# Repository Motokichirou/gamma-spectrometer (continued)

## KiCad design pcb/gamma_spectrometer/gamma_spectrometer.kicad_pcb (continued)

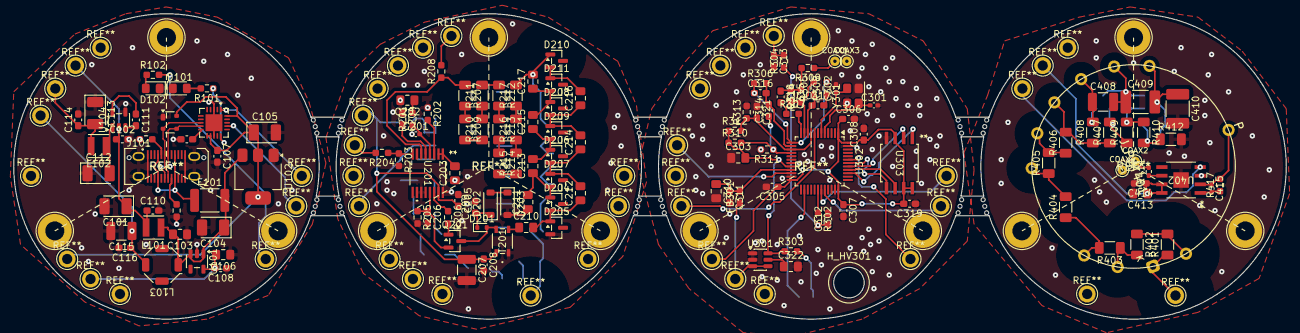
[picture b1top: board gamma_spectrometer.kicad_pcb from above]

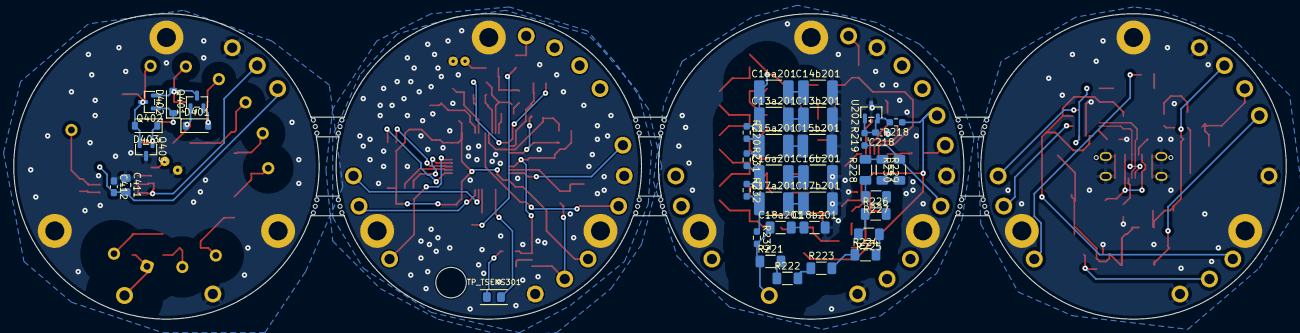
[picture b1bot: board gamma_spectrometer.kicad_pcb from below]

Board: 2 copper layers, 187.5 x 45.0 mm, 183 parts (39 on the bottom side), 115 nets.

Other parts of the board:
COAX1, COAX2, COAX3, COAX4: COAX_PIN_D0.5
H_HV301: HOLE_HV_WIRE_D5.0
PANEL1: PANEL_MOUSEBITES
TP_TSENS301: TP_TSENS_2x0805

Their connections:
AMP_OUT: COAX1.1, COAX2.1; also elsewhere on the board
GND: COAX3.1, COAX4.1; also elsewhere on the board
TSENS_IN: TP_TSENS301.2; also elsewhere on the board
TSENS_PWR: TP_TSENS301.1; also elsewhere on the board

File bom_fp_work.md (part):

# BOM — финальное состояние

> **Статус:** ВСЕ КОМПОНЕНТЫ НАЗНАЧЕНЫ ✅ (включая J_PMT401 — футпринт `J_PMT401_R1307-01` сделан, Ø30)
> Свежий нетлист: `pcb/gamma_spectrometer.net` (2026-06-24, 177 компонентов: 74 конд. + 63 рез. + активные/прочие)
> ⚠ **Правки 2026-08-07 ещё НЕ в нетлисте** (схему правит пользователь): R313 2к→14.7к, R311 5.9к→909,
> U301 TL431→REF35250 (SOT-23-6), R301 удалён, C303 100нФ→1мкФ, добавлен C322 1мкФ.
> После правки схемы: 75 конденсаторов, 62 резистора, всего 177.
> Свежий BOM: см. ниже / экспорт из KiCad

---

## Сводный BOM (финальный)

### Конденсаторы — 17 уникальных MPN, 74 шт

| Refs | Qty | Value | MPN | Footprint |
|---|---|---|---|---|
| C13a201, C13b201, C14a201, C14b201, C15a201, C15b201, C16a201, C16b201, C17a201, C17b201, C410 | 11 | 0.1uF / 1кВ | C1812X104K102T (Holy Stone) | C_1812_HandSolder |
| C18a201, C18b201 | 2 | 220pF / 1кВ C0G | CC1206JKNPOCBN221 (Yageo) | C_1206_HandSolder |
| C101, C104, C105, C112, C113 | 5 | 10uF тант. | TR3B106K010C0750 (Vishay) | CP_EIA-3528-21_Kemet-B_HandSolder |
| C102, C107-C111, C114, C116, C204, C205, C208, C218, C304-C309, C311-C314, C317, C319-C321, C412, C414 | 28 | 0.1uF X7R | CC0603JRX7R9BB104 (Yageo) | C_0603_HandSolder |
| C103, **C303**, **C322** | 3 | 1uF X7R | CC0805JKX7R9BB105 (Yageo) | C_0805_HandSolder — C303 выход REF35250 (обязателен 0.1…10 мкФ), C322 на вывод NR |
| C106, C310, C411, C413 | 4 | 4.7uF X5R | GRM21BR61C475KA88L (Murata) | C_0805_HandSolder |
| C115, C207 | 2 | 47uF X7R | GRM32ER71A476KE15L (Murata) | C_1210_HandSolder |
| C202 | 1 | 33nF X7R | CC0805JRX7R9BB333 (Yageo) | C_0805_HandSolder |
| C203 | 1 | 0.47uF X7R | CC0805JKX7R9BB474 (Yageo) | C_0805_HandSolder |
| C206, C315, C318 | 3 | 100pF C0G | CC0603JRNPO9BN101 (Yageo) | C_0603_HandSolder |
| C201 | 1 | 22pF C0G 50В | GRM1555C1H220JA01D (Murata) | C_0402_HandSolder — C_COMP2, добавлен 2026-09-20 |
| C209 | 1 | 10nF X7R — **заменить на 100 В** | CC0603KRX7R9BB103 (Yageo, 50 В) ⚠ | C_0603_HandSolder → 0805/100В |
| C210-C217 | 8 | 1nF / 500В C0G | CC0805JKNPOBBN102 (Yageo) | C_0805_HandSolder — ⚠ размах на ступень 310…385 В (4 ступени!), запас 1.3× при 1500 В |
| C301, C302 | 2 | 18pF C0G | CC0402FRNPO9BN180 (Yageo) | C_0402_HandSolder |
| C316 | 1 | 510pF C0G | CC0603FRNPO9BN511 (Yageo) | C_0603_HandSolder |
| C408 | 1 | 22nF / 1кВ | CC1210KKX7RCBB223 (Yageo) | C_1210_HandSolder |
| C409 | 1 | 47nF / 1кВ | GRM43DR73A473KW01L (Murata) | C_1812_HandSolder |
| C415 (Cf, TIA) | 1 | 4.7pF C0G NP0 | GRM1555C1H4R7CA01D (Murata) | C_0402_HandSolder |

### Резисторы — стандартные 0603 (1%, низковольтные)

| Refs | Qty | Value | MPN | Серия |
|---|---|---|---|---|
| R101, R102 | 2 | 330R | RT0603BRD07330RL | Yageo RT (thin film) |
| R201 | 1 | 1M | RT0603BRD071ML | Yageo RT (thin film) |
| R202 | 1 | 180k | RC0603FR-07180KL | Yageo RC |
| R203, R220, R231, R232 | 4 | 100k | RC0603FR-07100KL | Yageo RC |
| R204, R302-R305, R307, R309, R408, R411, R413 | 10 | 10k | RC0603FR-0710KL | Yageo RC (R303 = Pt1000 pull-up) |
| R205 | 1 | 0.1R | RL0603FR-070R1L | Yageo RL (current sense) |
| R206, R233 | 2 | 10R | AC0603FR-0710RL | Yageo AC (anti-surge) |
| R208 | 1 | 2.2M | RC0603FR-072M2L | Yageo RC |
| R218 | 1 | 1.2k | RC0603FR-071K2L | Yageo RC |
| R219 | 1 | 110k | RC0603FR-07110KL | Yageo RC |
| ~~R301~~ | — | ~~330R~~ | — | **УДАЛЁН 2026-08-07**: балласт шунта TL431 не нужен последовательной опоре REF35250 |
| R306, R308 | 2 | 1k | RC0603FR-071KL | Yageo RC |
| R310 | 1 | 22k | RC0603FR-0722KL | Yageo RC |
| R311 | 1 | **909R** | RC0603FR-07909RL | Yageo RC (было 5.9k; смена полярности 2026-08-07) |
| R312 | 1 | 8.2k | RC0603FR-078K2L | Yageo RC |
| R313 | 1 | **14.7k** | RC0603FR-0714K7L | Yageo RC (было 2k; смена полярности 2026-08-07) |
| R417 (Rf, TIA) | 1 | 499R | RC0603FR-07499RL | Yageo RC (вход TIA; Rin/Rg R415/R416 убраны) |
| R_CC101, R_CC102 | 2 | 5.1k | RC0603FR-075K1L | Yageo RC |

**Все 0603 footprint:** Resistor_SMD:R_0603_1608Metric_Pad0.98x0.95mm_HandSolder

### Резисторы — высоковольтные 1206

| Refs | Qty | Value | MPN | Серия |
|---|---|---|---|---|
| R207, R209-R217 | 10 | 100M | RC1206JR-07100ML (5%) | Yageo RC |
| R221-R230 | 10 | 6.8M | RC1206FR-076M8L (1%) | Yageo RC |
| R401, R402 | 2 | 750k | RC1206FR-07750KL | Yageo RC |
| R403-R406 | 4 | 680k | RC1206FR-07680KL | Yageo RC |
| R407, R408 | 2 | 1.3M | RC1206FR-071M3L | Yageo RC (база+эмиттер буфера Q401, пересборка по Fig 5-15) |
| R409 | 1 | 1.6M | RC1206FR-071M6L | Yageo RC |
| R410 | 1 | 2M | RC1206FR-072ML | Yageo RC |
| R412 | 1 | 2M | RC1206FR-072ML | Yageo RC (фикс C1: R414/mid_P убраны) |

**Все 1206 footprint:** Resistor_SMD:R_1206_3216Metric_Pad1.30x1.75mm_HandSolder

### Активные / разное

| Refs | Qty | Value | MPN | Footprint |
|---|---|---|---|---|
| D101 | 1 | LED синий | FYLS-0805UBC (Foryard) | LED_0805_HandSolder |
| D102 | 1 | LED зелёный | 150080GS75000 (Würth) | LED_0805_HandSolder |
| D201 | 1 | BAS516 | BAS516 (YJ) | D_SOD-523 |
| D202, D203 | 2 | BZT52C18 | BZT52C18 (Diotec) | Nexperia_CFP3_SOD-123W ⚠ проверить |
| D204-D211 | 8 | BAV23S | BAV23S (Nexperia) | SOT-23 |
| D401-D403 | 3 | 1N4148W | 1N4148W (onsemi/Diotec) | Diode_SMD:D_SOD-123 (защита B-E буферов Q401-403) |
| F101 | 1 | PTC 500мА | MF-MSMF050-2 (JEMETE) | Fuse_1812_HandSolder |
| FB301 | 1 | 120Ω@100МГц | BLM18EG121SN1D (Murata) | L_0603_HandSolder |
| J101 | 1 | USB-C | DX07S024WJ3R400 (JAE) | USB_C_Receptacle_JAE |
| J_PMT401 | 1 | ФЭУ R1307-01 | — | **J_PMT401_R1307-01** (своя библ. «посадочные места», Ø30, 18 слотов, готов) |
| L101, L102 | 2 | 47uH | SRN3015-470M (Bourns) | L_Neosid_SMS-ME3015 |
| L103 | 1 | 100uH | SRU5028-101Y (Bourns) | L_Bourns_SRU5016_5.2x5.2mm |
| Q201 | 1 | **IRLML0060** (60 В) | IRLML0060 (HOTTECH) | SOT-23 — ⛔ не IRLML0040: 40 В мало для выброса стока 43–45 В |
| Q401-Q403 | 3 | MMBTA42 | MMBTA42 (Diotec) | SOT-23 |
| T201 | 1 | 1:10.2 трансф. | ATB322524-0110-T000 (TDK) | CHOKE_524-0110-T000_TDK-M |
| U101 | 1 | LP5907MFX-3.3 | LP5907MFX-3.3 (TECH PUB) | SOT-23-5 |
| U102 | 1 | AMS1117-3.3 | AMS1117-3.3 (YOUTAI) | SOT-223-3 |
| U103 | 1 | FT231XQ | FT231XQ | QFN-20-1EP_4x4mm |
| U104 | 1 | TPS60400DBV | TPS60400DBV (TI) | SOT-23-5 |
| U201 | 1 | MAX1847EEE+ | MAX1847EEE+ (AliExpress) | QSOP-16 (21-0055H_16_MXM-M) |
| U202 | 1 | TL431 | TL431 (YOUTAI) | SOT-23 |
| **U301** | 1 | **REF35250** | **REF35250QDBVR** (TI) | **SOT-23-6 (DBV)** — опора 2.5 В, 12 ppm/°C |
| U302 | 1 | STM32G474CBT6 | STM32G474CBT6 (ST) | LQFP-48 |
| U303 | 1 | W25Q64JVSSIQ | W25Q64JVSSIQ (Winbond) | SOIC-8 |
| U402 | 1 | ADA4817-1ARDZ | ADA4817-1ARDZ (ADI) | SOIC-8 RD-8-4 (RD_8_1_ADI-M) — TIA вход |
| U_ESD101 | 1 | PRTR5V0U2X | PRTR5V0U2X (YOUTAI) | SOT-143 |
| Y301 | 1 | кварц 16МГц | ABM8G-16.000MHZ-4Y-T3 (Abracon) | Crystal_SMD_3225-4Pin |
| (внешн.) | 1 | Pt1000 термодатчик | 700-102BAA-B00 (Honeywell, артикул 32208572) | M222 leaded, не на PCB — крепится на корпус кристалла, витой парой к TSENS_PWR/TSENS_IN |

---

## ⚠ К проверке перед заказом

1. **🔴 D202, D203 footprint SOD-123W — ОБЯЗАТЕЛЬНО ИСПРАВИТЬ** — BZT52C18 от Diotec в стандартном SOD-123 (2.6×1.5мм). SOD-123W (3.7×1.6мм) шире на 0.8мм. Диоды не пропаяются на широком footprint. Поменять на `Diode_SMD:D_SOD-123`.

2. **U301 заменён на REF35250QDBVR** (2026-08-07, по ревью): параметрический шунт TL431 → последовательная опора,
   12 ppm/°C вместо 50 (у клона YOUTAI до 300). Дрейф калибровки на ±30 °C: 0.9 % → **0.036 %**. Критично потому,
   что эта опора задаёт и шкалу АЦП (`VREF+`), и рабочие точки шейпера (делители A/B).
   **U202 на ВВ-плате остаётся TL431** — он питает только делитель мониторинга ВВ, в энергошкале не участвует.

3. ~~R412, R414 URL~~ — ✅ исправлено.

4. ~~J_PMT401~~ — ✅ сделан `J_PMT401_R1307-01` в библиотеке «посадочные места» (по реальному обмеру: 11 pad, окружность выводов Ø35→**Ø30** под стойки, 18 слотов × 20°, отверстие Ø1.0 под вывод Ø0.7). Проверить линейкой в редакторе перед заказом.

---

## Дальнейшие этапы

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
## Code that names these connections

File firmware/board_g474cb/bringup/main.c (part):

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 * Без HAL, на регистрах CMSIS. Прошивается по UART через системный загрузчик.
 *
 * Делает:
 *   - сразу прижимает ВВ: PB10 (HV_ENABLE) = 0, PA8 (HV_CONTROL) = 0;
 *   - USART1 PA9/PA10, 115200 8N1 (через FT231X на USB-плате);
 *   - печатает DEV_ID, объём флеш, корпус, FLASH_OPTR;
 *   - запускает HSE (кварц 16 МГц) и переводит на него SYSCLK —
 *     если после перехода текст читается, кварц на 16 МГц исправен;
 *   - раз в секунду: статус (VREF+, ВВ); D102 = индикатор ВВ;
 *   - ВВ: ШИМ PA8 31 кГц, монитор PA0, подстройка, защита; команды hv/hvzero/a/n/d (см. help);
 *   - по строке "!boot" прыгает в системный загрузчик (для следующих прошивок без BOOT0).
 */
#include <stdint.h>
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    RCC->AHB2ENR |= RCC_AHB2ENR_GPIOAEN | RCC_AHB2ENR_GPIOBEN;
    (void)RCC->AHB2ENR;

    /* ВВ выключено: PB10 = 0, PA8 = 0, оба выходы push-pull */
    GPIOB->BSRR = 1u << (10 + 16);
    GPIOB->MODER = (GPIOB->MODER & ~(3u << 20)) | (1u << 20);
    GPIOA->BSRR = 1u << (8 + 16);
    GPIOA->MODER = (GPIOA->MODER & ~(3u << 16)) | (1u << 16);

    /* LED D102: PB6 выход */
    GPIOB->BSRR = 1u << (6 + 16);
    GPIOB->MODER = (GPIOB->MODER & ~(3u << 12)) | (1u << 12);

    /* USART1: PA9 TX, PA10 RX, AF7, подтяжка на RX */
    GPIOA->AFR[1] = (GPIOA->AFR[1] & ~((15u << 4) | (15u << 8))) | (7u << 4) | (7u << 8);
    GPIOA->PUPDR = (GPIOA->PUPDR & ~(3u << 20)) | (1u << 20);
    GPIOA->MODER = (GPIOA->MODER & ~((3u << 18) | (3u << 20))) | (2u << 18) | (2u << 20);
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}
static uint32_t adc_vrefint(void) { return adc_read(ADC1, 18); }

/* ОУ тракта: OPAMP1 и OPAMP2 — внешняя обвязка (VINP0/VINM0), OPAMP3 — PGA x4 от PB0 */
static void opamp_init(void)
{
    RCC->APB2ENR |= RCC_APB2ENR_SYSCFGEN;
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    OPAMP3->CSR = OPAMP_CSR_OPAMPxEN | (2u << OPAMP_CSR_VMSEL_Pos) | OPAMP_CSR_PGGAIN_0;
    /* Pt1000: узел ~0.25 В -> x8 -> ~2 В на ADC4; 1 LSB = 0.09 °C вместо 0.75 (2026-11-06) */
    OPAMP6->CSR = OPAMP_CSR_OPAMPxEN | (2u << OPAMP_CSR_VMSEL_Pos) | (2u << OPAMP_CSR_PGGAIN_Pos) |
                  OPAMP_CSR_OPAMPINTEN;   /* VPSEL = 0: PB12 */
}

static void report(uint32_t vref_mv)
{
    static const struct { const char *name; uint8_t adc2; uint8_t ch; const char *exp; } t[] = {
        { "PA0 HV_MONITOR ", 0,  1, "~2440 (HV=0)" },
        { "PA1 V_A (OA1+) ", 0,  2, "1616" },
        { "PA3 OA1-       ", 0,  4, "1616" },
        { "PA2 OA1 out    ", 0,  3, "~2420" },
        { "PA7 V_A (OA2+) ", 1,  4, "1616" },
        { "PA5 OA2-       ", 1, 13, "1616" },
        { "PA6 OA2 out    ", 1,  3, "~1616" },
        { "PB0 V_B (OA3+) ", 0, 15, "99" },
        { "PB1 OA3 out ADC", 0, 12, "~400" },
        { "PB12 TSENS_IN  ", 0, 11, "?" },
    };
    uart_puts("---- analog, mV (expected) ----\n");
    for (unsigned i = 0; i < sizeof t / sizeof t[0]; i++) {
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{
    GPIOB->BSRR = 1u << (10 + 16); /* ВВ выкл. */
    GPIOA->BSRR = 1u << (8 + 16);
    GPIOA->MODER = (GPIOA->MODER & ~(3u << 16)) | (1u << 16); /* PA8: ШИМ -> выход 0 */
    TIM1->CR1 = 0; TIM1->BDTR = 0;
    RCC->APB2RSTR |= RCC_APB2RSTR_TIM1RST; RCC->APB2RSTR &= ~RCC_APB2RSTR_TIM1RST;
    RCC->APB2ENR &= ~RCC_APB2ENR_TIM1EN;
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    while (((RCC->CFGR & RCC_CFGR_SWS) >> RCC_CFGR_SWS_Pos) != 1u) {}
    RCC->CR &= ~(RCC_CR_PLLON | RCC_CR_HSEON);

    /* PA9/PA10 вернуть в аналоговый режим (как после сброса); PB10/PA8 остаются выходами 0 */
    GPIOA->MODER |= (3u << 18) | (3u << 20);

    RCC->APB2ENR |= RCC_APB2ENR_SYSCFGEN;
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

/* ===================== Управление ВВ =====================
 * HV_CONTROL: PA8 = TIM1_CH1 (AF6), ШИМ 12 бит, 16 МГц / 4096 = 3.9 кГц,
 *             фильтр R302/C312 + R304/C313 (2 x 10к/100н). Амплитуда ШИМ = +3.3V_D,
 *             меряется по каналу VBAT (VBAT на плате = +3.3V_D), ADC1_IN17 = VBAT/3.
 * Уставка:    |V_cw| = 454.5 * V_CONTROL (FB с CW_out; −HV_out под нагрузкой ≈ 0.96 от уставки).
 * HV_ENABLE:  PB10, активный HIGH.
 * Монитор:    PA0 = ADC1_IN1 (с −HV_out), |V| = (zero − V_mon) / 1.615 мВ/В, zero ≈ 2460 мВ.
 */
#define HV_K_SET     454.5f
#define HV_K_MON     1.640f     /* калибровка мультиметром 2026-11-05: −455 В при V_mon 1714 мВ, zero 2460 (расчёт 1.615) */
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    TIM1->BDTR = TIM_BDTR_MOE;
    TIM1->EGR = TIM_EGR_UG;
    TIM1->CR1 = TIM_CR1_ARPE | TIM_CR1_CEN;
    GPIOA->AFR[1] = (GPIOA->AFR[1] & ~15u) | 6u;                 /* PA8 -> AF6 при CCR1 = 0 */
    GPIOA->MODER = (GPIOA->MODER & ~(3u << 16)) | (2u << 16);
}

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}

static const struct { const char *nm; uint8_t adc2, ch; } npt[] = {
    { "PB1", 0, 12 }, { "PA1", 0, 2 }, { "PA3", 0, 4 }, { "PA2", 0, 3 },
    { "PA7", 1, 4 }, { "PA5", 1, 13 }, { "PA6", 1, 3 }, { "PB0", 0, 15 }, { "PA0", 0, 1 }, { "VREFINT", 0, 18 }, { "VBAT", 0, 17 },
};
static int noise_pt(const char *a, uint32_t vref_mv)
{
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    return 0;
}

/* Pt1000: R303 10к от VREF+ -> узел -> Pt1000 -> GND; узел на PB12 = ADC1_IN11.
 * Ратиометрично: R = 10к * raw / (4095 - raw), опора сокращается.
 * T по Каллендару — Ван Дюзену (T >= 0): R = R0 (1 + A T + B T^2). */
#define PT_R0    1000.0f
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        uart_puts("DUMP 8192\n");
        for (int i = 0; i < 8192; i++) { uart_hex(nbuf[i], 3); if ((i & 31) == 31) uart_puts("\n"); }
        uart_puts("END\n");
    } else if (l[0] == 'n' && (l[1] == 0 || l[1] == ' ')) {   /* n [PB1|PA1|PA3|PA2|PA7|PA5|PA6|PB0|PA0] */
        if (!noise_pt(l[1] ? l + 2 : "", vref_mv)) help();
    } else if (l[0] == 'a' && l[1] == 0) {
        report(vref_mv);
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
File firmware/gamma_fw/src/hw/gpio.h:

/* gpio.h — безопасное состояние выводов (SPEC §1, §3). */
#ifndef GPIO_H
#define GPIO_H

/* ПЕРВЫМ после сброса: PB10 (HV_ENABLE) = 0, PA8 (HV_CONTROL) = 0, PB6 (D102) = 0 — выходы
   push-pull; прочие выводы GPIOA/B/C — в аналог (как после сброса), кроме оставленных как есть:
   PA13/PA14 (SWD), PA15/PB3/PB4 (W25Q64: до spiflash_sleep /CS держит подтяжка вверх по сбросу; после — PA15
   выход 1, PB3/PB4 аналог).
   Нужна и после перехода из системного загрузчика по Go: он мог оставить PA8 как I2C2_SDA
   с подтяжкой вверх, USART1 на PA9/PA10 и т. п. */
void gpio_safe_init(void);

/* ВВ выкл немедленно: PB10 = 0, PB6 = 0, PA8 — выход 0 (из AF ШИМ). Без стека и прерываний —
   годится в обработчике сбоя и перед переходом в загрузчик. Таймер TIM1 не трогает. */
void gpio_hv_force_off(void);

#endif

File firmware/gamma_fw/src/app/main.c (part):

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 * Учёт времени набора, живого времени и скоростей — core/acq.c; там же команды -smp, -noise, -osc.
 *
 * Задача 10 мс: adc_aux_poll → svc_aux_10ms (монитор, мВ; NaN — замер устарел) → hv_tick →
 * hvpwm_set, hv_enable_pin(hv_enabled). Задача 1 с: svc_aux_1s (VREF+ 2500 ± 30 мВ — иначе
 * ВВ не включается, при включённом — выкл; при выключенном — перекалибровка АЦП), +3.3V_D τ 60 с,
 * Pt1000 τ 10 с → термокомпенсация (det_set_gain) и T1 в -inf; скорости и загрузка ЦП (acq_tick_1s).
 *
 * Task 11: тестовые импульсы ЦАП (-dac, core/dactest + hw/dac_test: TIM6 в прерывании пишет DAC1 на
 * PA4; по окончании серии — текст "-ok dac done <n>", PA4 снова Hi-Z). Добавка к периоду — один
 * отсчёт АЦП в тактах ЦП (45 при 2.5 такта, 57 при 6.5), чтобы фаза ступеньки была равномерной.
 * На время серии детектор — в режиме самотеста ЦАП (эталон tpl_dac, ширина, база заморожена).
 *
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}

/* ---- порт proto ---- */
static void p_tx(const uint8_t *p, size_t n) { uart_tx(p, n); }
static size_t p_tx_free(void) { return uart_tx_free(); }
static uint32_t p_millis(void) { return millis(); }
/* запись настроек во флеш: стирание страницы останавливает ЦП на ~25 мс — в наборе нельзя
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    dac_test_stop();
    hv_off(&hv, "boot");
    hvpwm_set(0);
    hv_enable_pin(false);
    /* во время набора в кольце UART до 8 КБ спектра (≈ 140 мс при 600 000): дослать их ДО ответа, иначе
       boot_enter_system (ждёт 50 мс) сбросит USART раньше, чем уйдёт "-ok boot", хост повторит "!boot"
       уже загрузчику — тот по чужому байту настроит скорость и не узнает 0x7F (найдено 2026-11-10) */
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    float mon = svc_aux_10ms(&aux, ar.mon_raw, ar.mon_new, hv_enabled(&hv), now);
    hv_duty = hv_tick(&hv, mon, aux.vdd_mv, now);
    hvpwm_set(hv_duty);
    hv_enable_pin(hv_enabled(&hv));
}

/* автозапуск ВВ собранного блока (-hvboot, SPEC §3): один раз за пуск, после HV_AUTO_MS, когда опора,
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                                sec_vbat_new ? sec_vbat : NAN, sec_pt_new ? sec_pt : NAN);
        sec_vrefint_new = sec_vbat_new = sec_pt_new = false;
        hv_set_vref(&hv, svc_vref_mv(&aux));
        if (!hv_enabled(&hv)) { hv_duty = 0; hvpwm_set(0); hv_enable_pin(false); }  /* выкл по VREF+ — сразу */
        hv_autostart(millis());
        if (recal) {                           /* опора не устоялась к калибровке (SPEC §3.3) */
            adc_aux_recalibrate();
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
int main(void)
{
    gpio_safe_init();                          /* ПЕРВЫМ: PB10 = PA8 = PB6 = 0 — ВВ и D102 выкл (SPEC §3) */
    /* после Go загрузчика могли остаться его прерывания — наши векторы их не ждут
       (PRIMASK уже взведён в SystemInit) */
    __disable_irq();
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    uart_init(HW_UART_BAUD);
    __enable_irq();
    opamp_init();                              /* тракт и Pt1000 — сразу: устоятся к запуску АЦП */
    hv_enable_pin(false);
    hvpwm_init();                              /* CCR1 = 0: PA8 из «выход 0» в AF без выброса */

    /* настройки: пусто/битые/другая версия/DBANK = 1 → умолчания (Review Focus 1) */
    bool fl_ok = flash_settings_load(&live);
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
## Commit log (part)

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2026-05-21 Initial commit: NaI(Tl) gamma spectrometer project
    - KiCad schematics for all 4 boards (USB/Power, HV, MCU, Divider)
    - LTspice simulations (AD8000, CR-RC2 shaper, noise)
    - Documentation and datasheets
    - BOM and footprint work in progress
    - Host software skeleton (shproto)
2026-05-21 Update session_context: session 4, shproto full spec, GitHub setup
2026-05-22 Update session_context: footprint/MPN workflow agreed
